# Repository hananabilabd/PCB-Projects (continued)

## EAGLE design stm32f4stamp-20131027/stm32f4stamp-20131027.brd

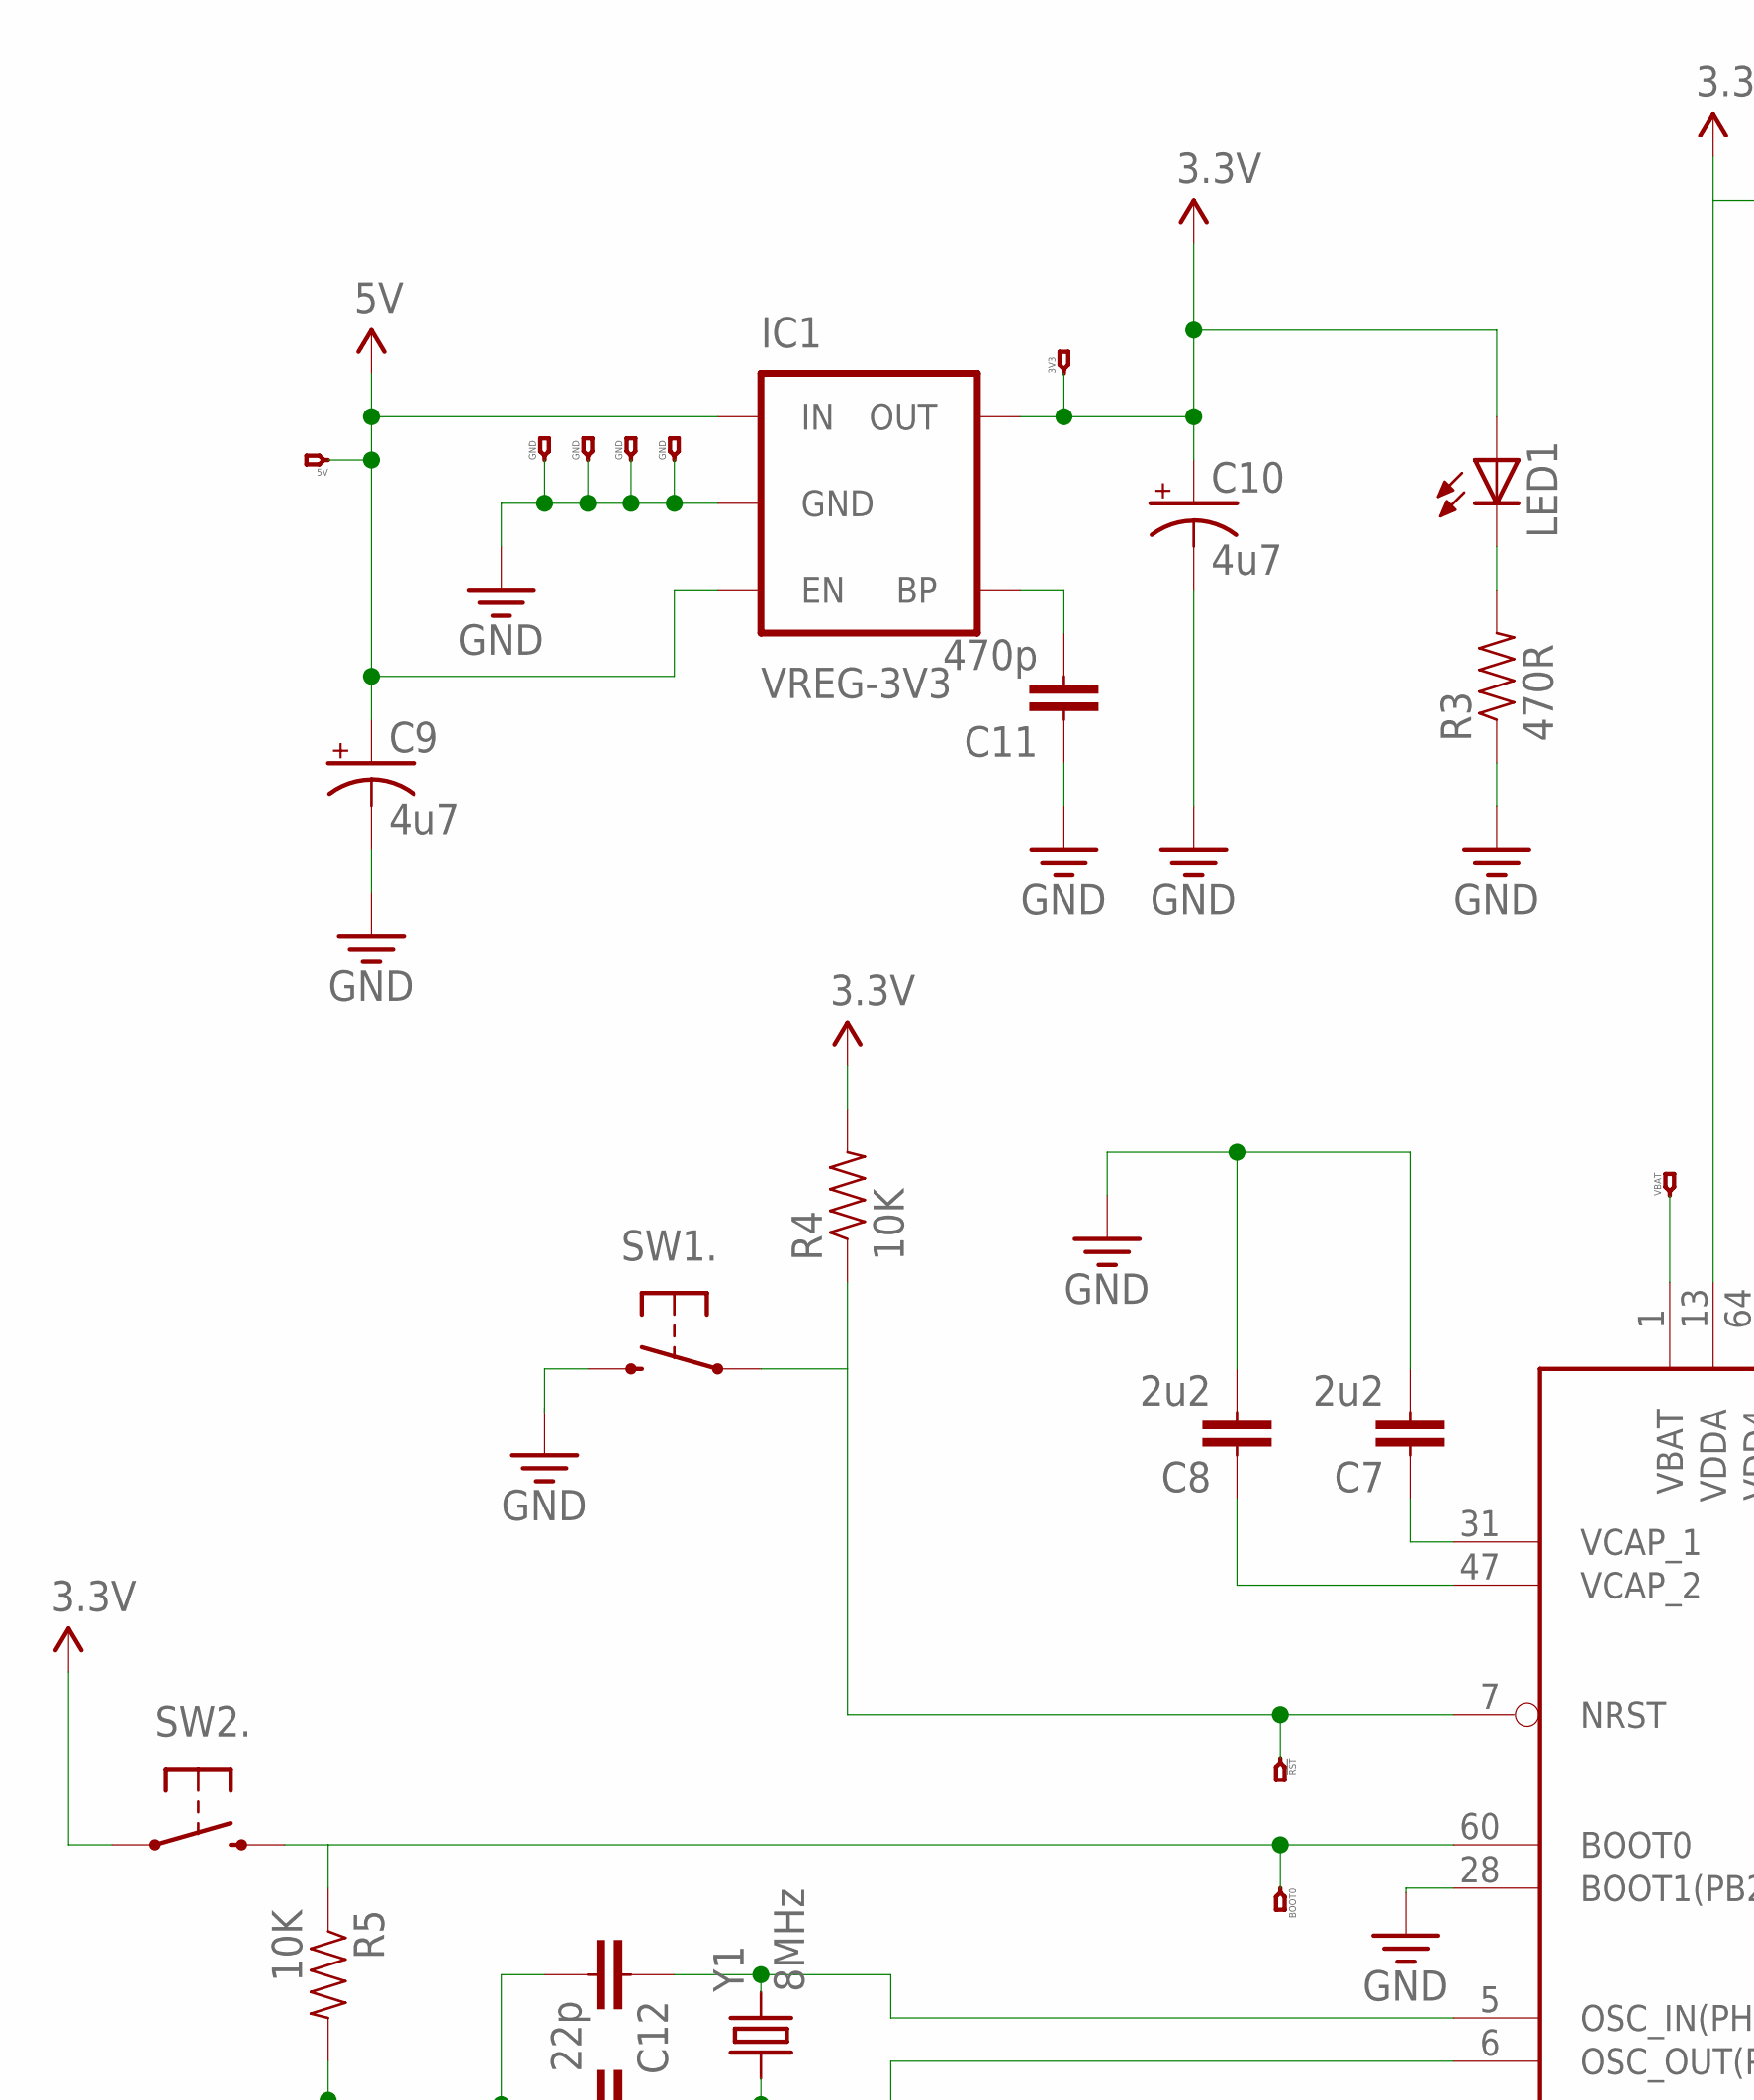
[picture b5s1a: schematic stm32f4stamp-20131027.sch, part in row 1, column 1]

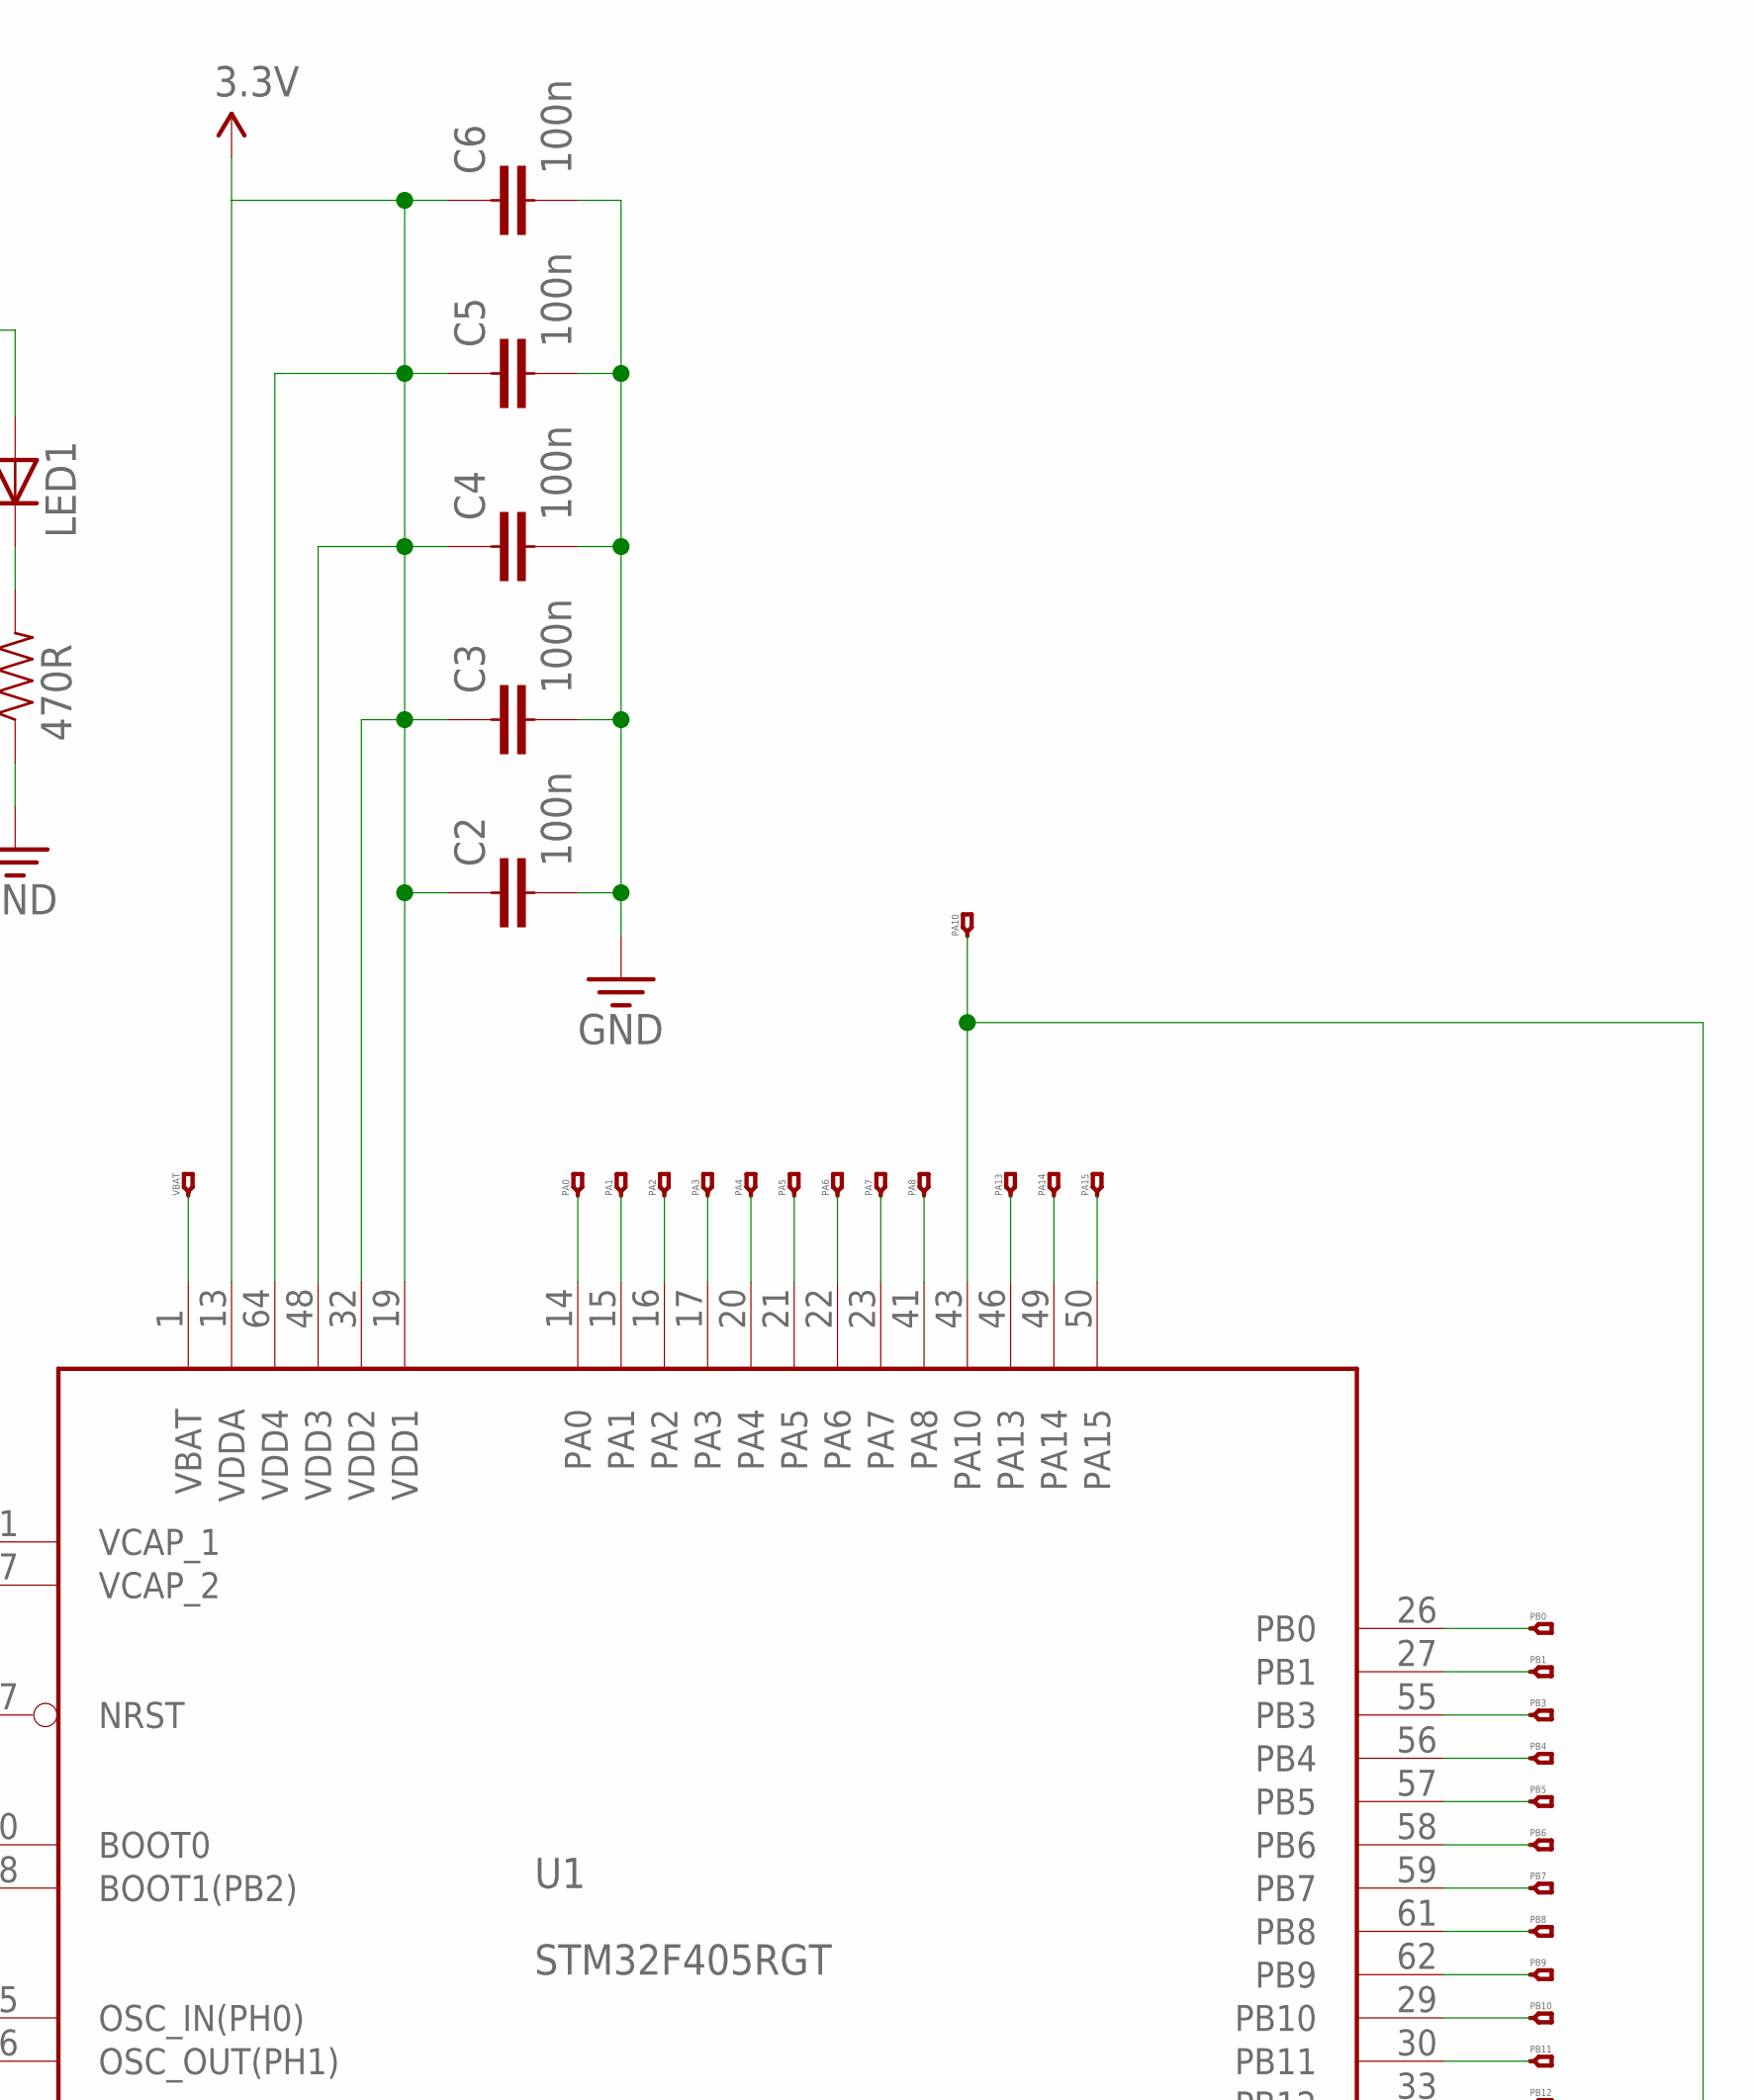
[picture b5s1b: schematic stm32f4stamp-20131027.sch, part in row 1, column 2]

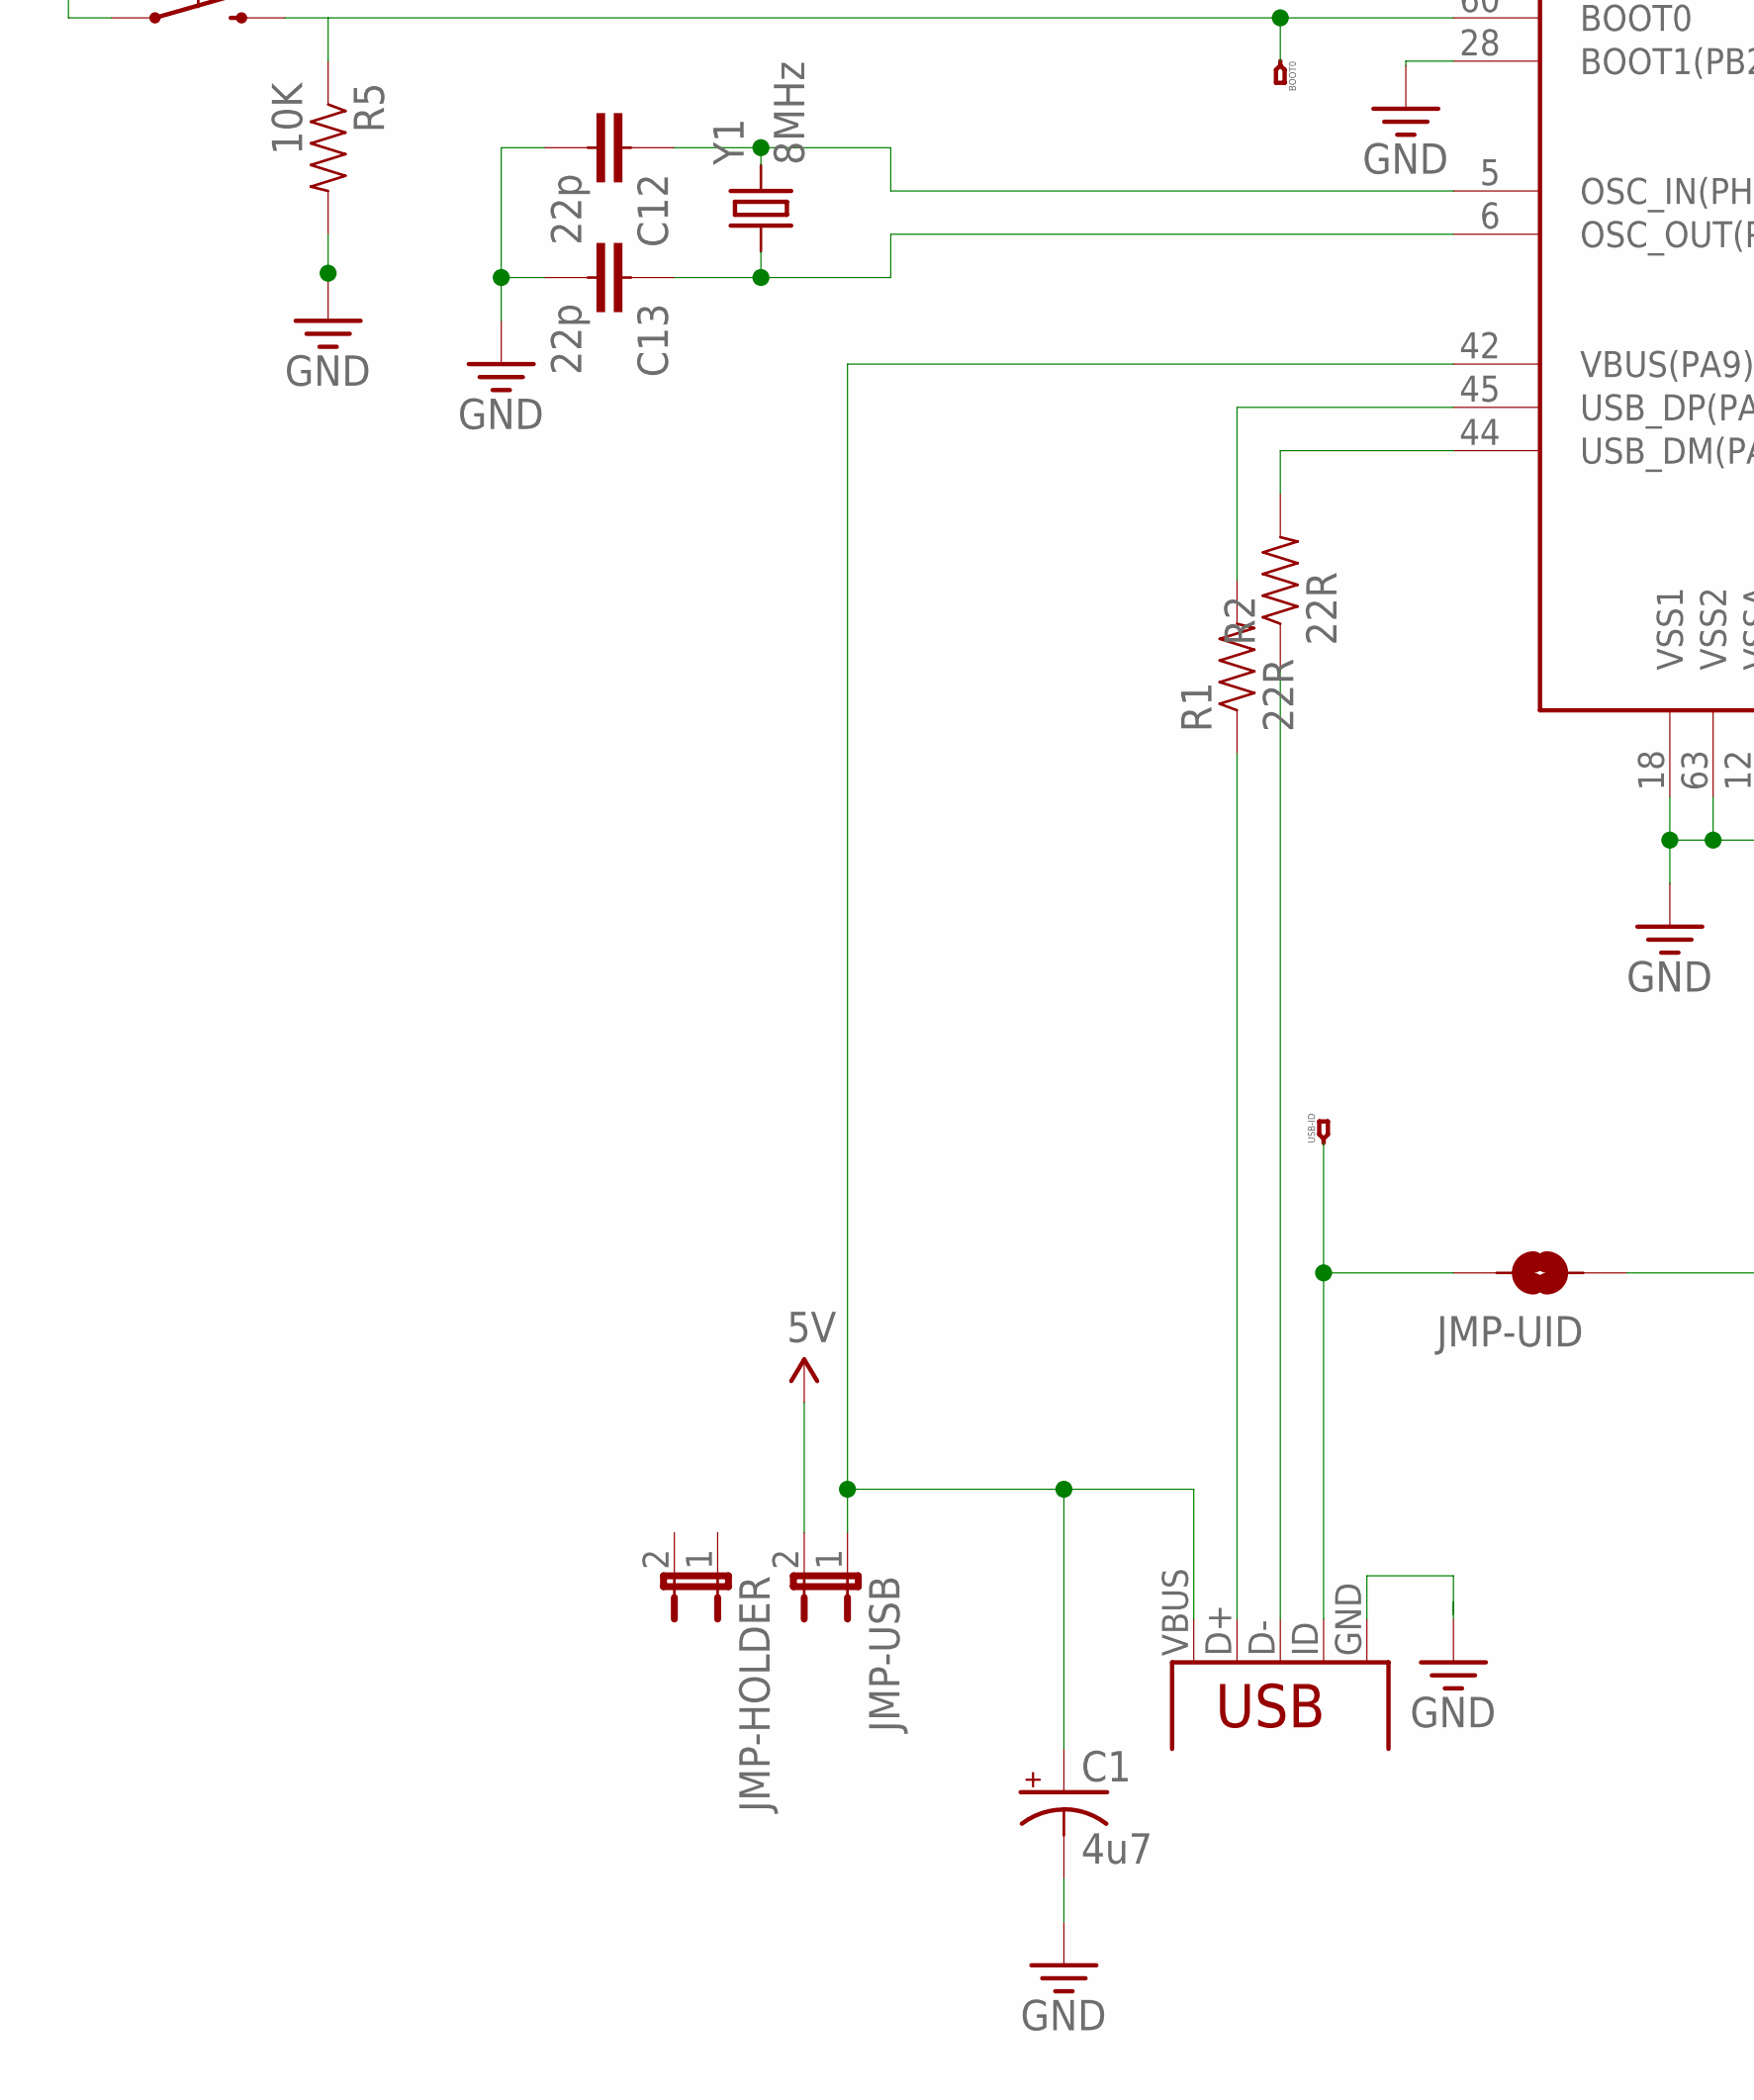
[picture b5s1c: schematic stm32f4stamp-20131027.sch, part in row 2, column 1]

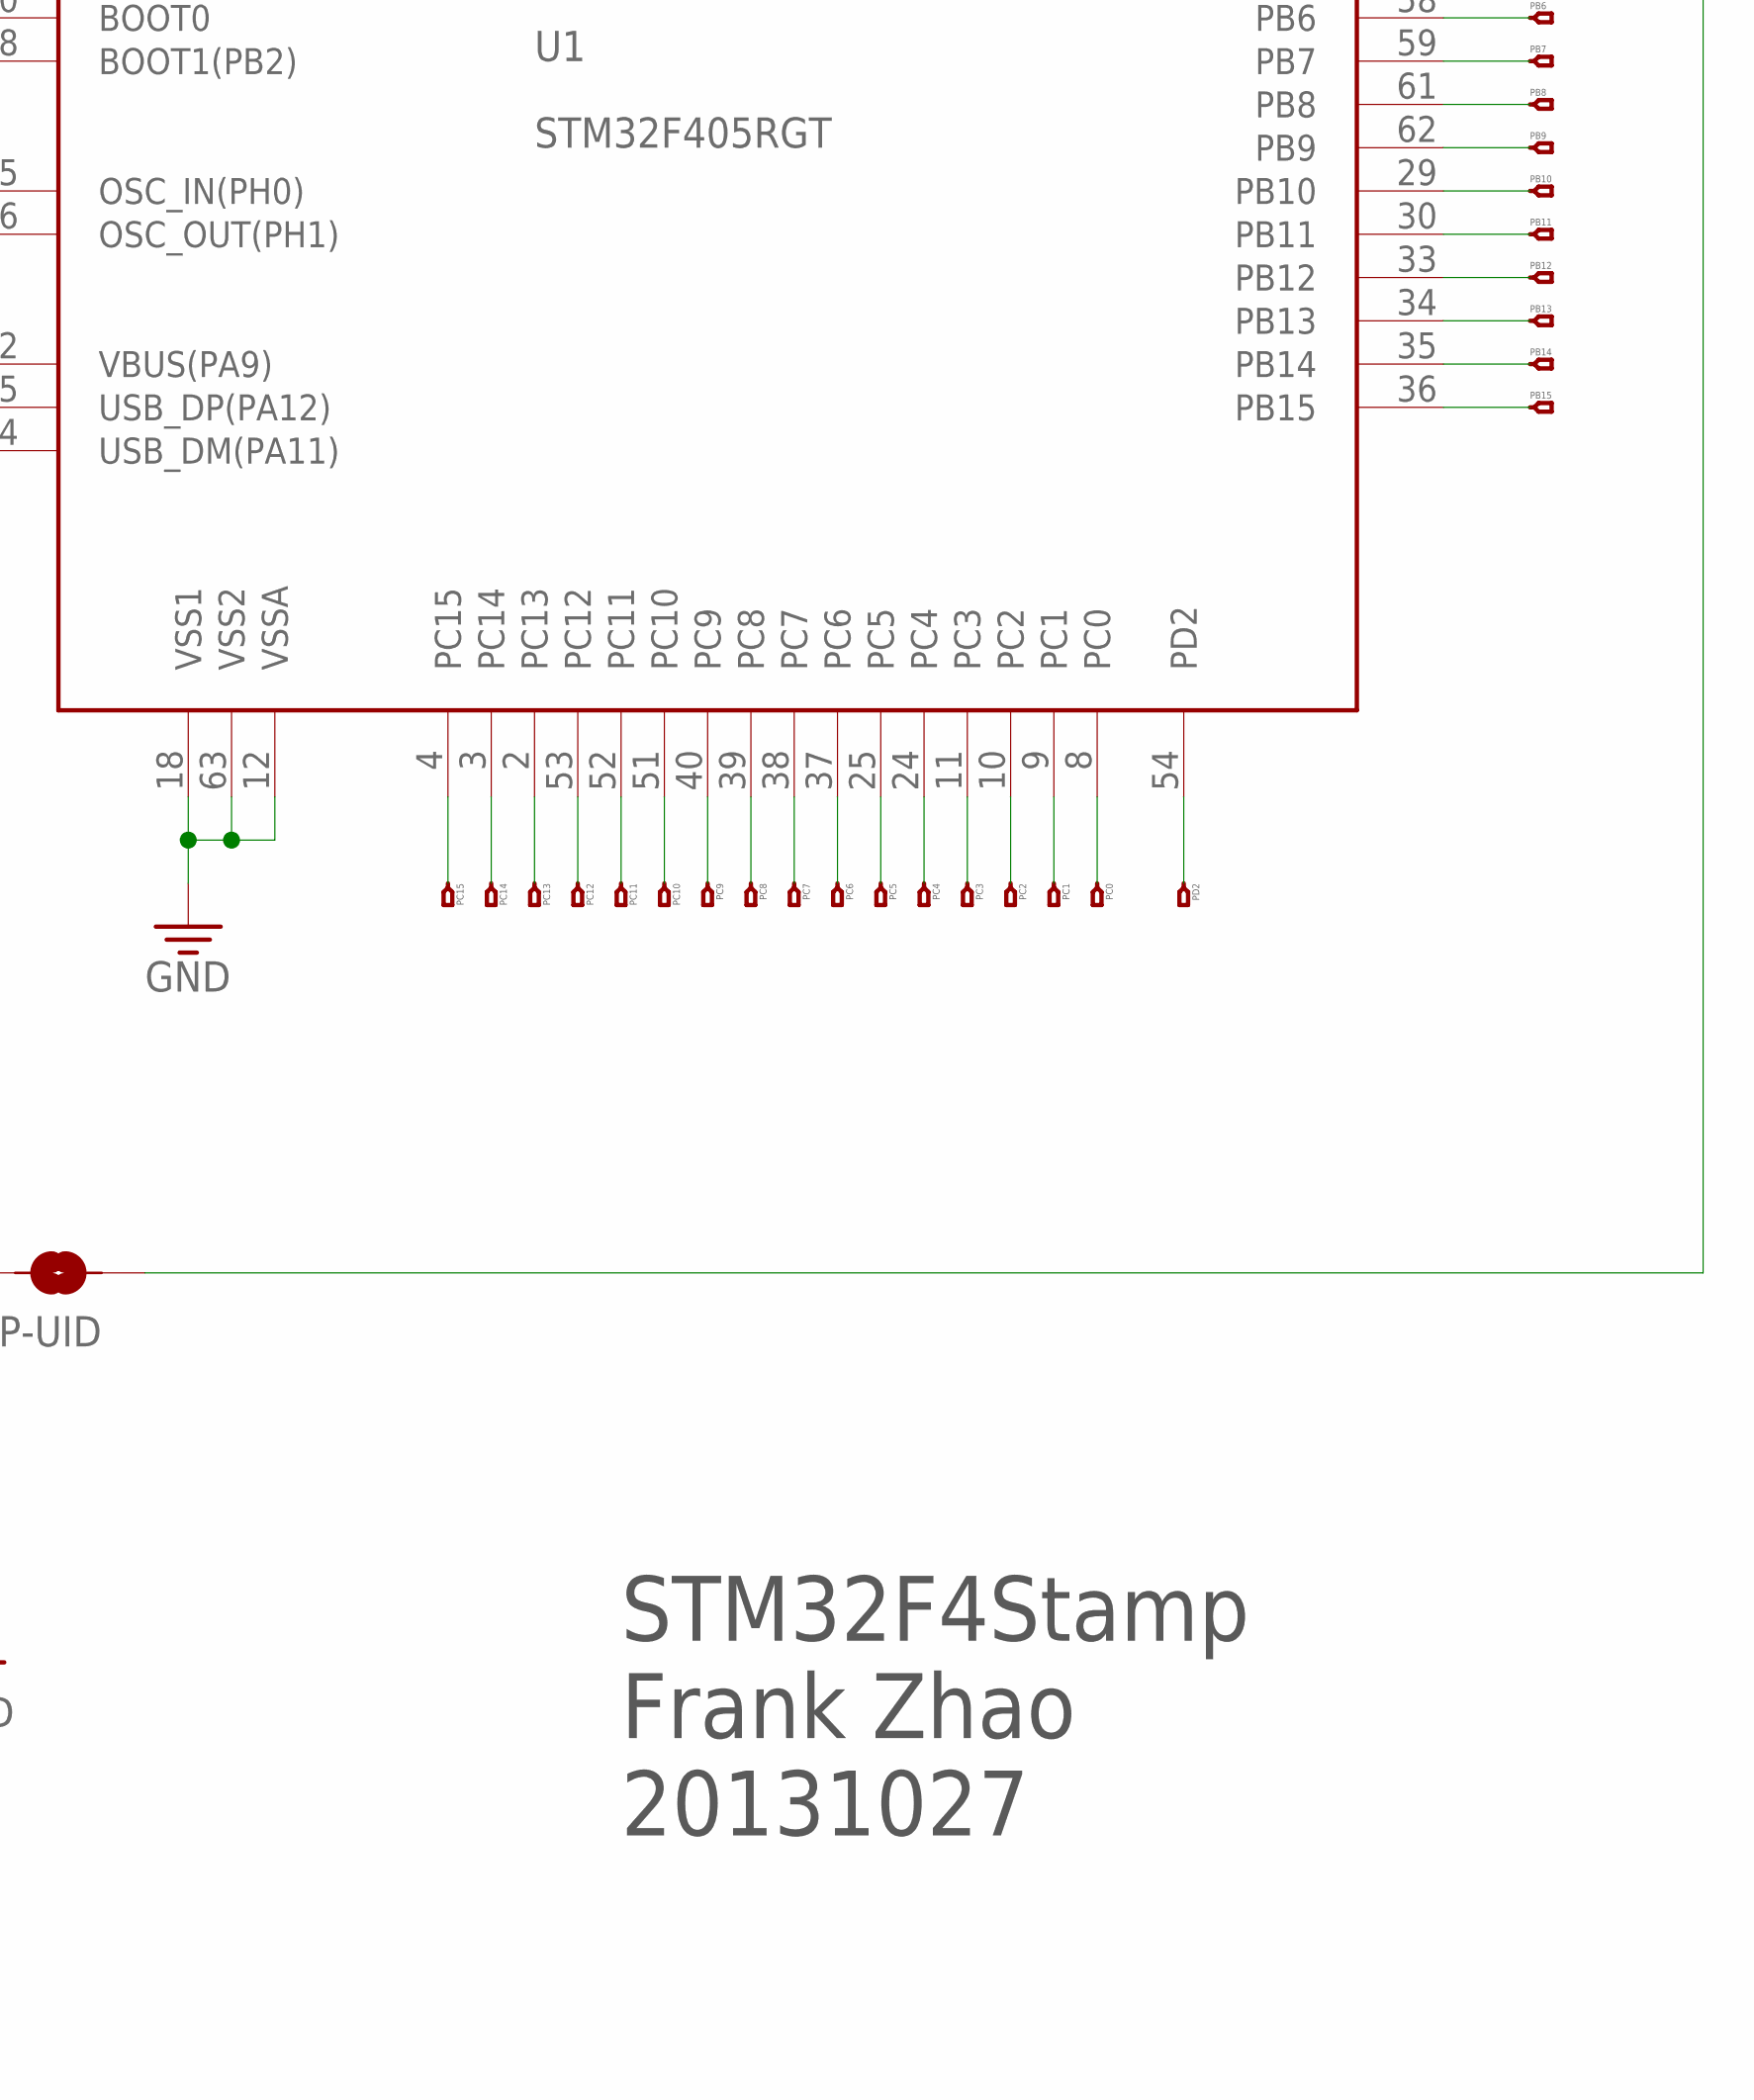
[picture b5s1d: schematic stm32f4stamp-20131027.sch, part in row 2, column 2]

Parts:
C1, C9, C10: 4u7; EIA3216-KIT
C2, C3, C4, C5, C6: 100n; 0603-CAP
C7, C8: 2u2; 0603-CAP
C11: 470p; 0603-CAP
C12, C13: 22p; 0603-CAP
IC1: VREG-3V3; SOT23-5
JMP-HOLDER: JUMPER-2-PTH-2MM; 1X02_2MM_TH
JMP-UID: SOLDERJUMPERNC; SJ_2S
JMP-USB: JUMPER-2-PTH-2MM; 1X02_2MM_TH
JP2: 5V; 1X1-HEADER-HOLE
JP3, JP5, JP6, JP7: GND; 1X1-HEADER-HOLE
JP4: 3V3; 1X1-HEADER-HOLE
JP8: PB8; 1X1-HEADER-HOLE
JP9: PA10; 1X1-HEADER-HOLE
JP10: PA8; 1X1-HEADER-HOLE
JP11: PA13; 1X1-HEADER-HOLE
JP12: PC9; 1X1-HEADER-HOLE
JP13: PC15; 1X1-HEADER-HOLE
JP14: PC14; 1X1-HEADER-HOLE
JP15: PC13; 1X1-HEADER-HOLE
JP16: PC12; 1X1-HEADER-HOLE
JP17: PC11; 1X1-HEADER-HOLE
JP18: PC10; 1X1-HEADER-HOLE
JP19: PC8; 1X1-HEADER-HOLE
JP20: PC7; 1X1-HEADER-HOLE
JP21: PC6; 1X1-HEADER-HOLE
JP22: PC5; 1X1-HEADER-HOLE
JP23: PC4; 1X1-HEADER-HOLE
JP24: PC3; 1X1-HEADER-HOLE
JP25: PC2; 1X1-HEADER-HOLE
JP26: PC1; 1X1-HEADER-HOLE
JP27: PC0; 1X1-HEADER-HOLE
JP28: PD2; 1X1-HEADER-HOLE
JP29: PA0; 1X1-HEADER-HOLE
JP30: PA1; 1X1-HEADER-HOLE
JP31: PA2; 1X1-HEADER-HOLE
JP32: PA3; 1X1-HEADER-HOLE
JP33: PA4; 1X1-HEADER-HOLE
JP34: PA5; 1X1-HEADER-HOLE
JP35: PA6; 1X1-HEADER-HOLE
JP36: PA7; 1X1-HEADER-HOLE
JP37: PA14; 1X1-HEADER-HOLE
JP38: PA15; 1X1-HEADER-HOLE
JP39: PB0; 1X1-HEADER-HOLE
JP40: PB1; 1X1-HEADER-HOLE
JP41: PB3; 1X1-HEADER-HOLE
JP42: PB4; 1X1-HEADER-HOLE
JP43: PB5; 1X1-HEADER-HOLE
JP44: PB6; 1X1-HEADER-HOLE
JP45: PB7; 1X1-HEADER-HOLE
JP46: PB9; 1X1-HEADER-HOLE
JP47: PB10; 1X1-HEADER-HOLE
JP48: PB11; 1X1-HEADER-HOLE
JP49: PB12; 1X1-HEADER-HOLE
JP50: PB13; 1X1-HEADER-HOLE
JP51: PB14; 1X1-HEADER-HOLE
JP52: PB15; 1X1-HEADER-HOLE
JP53: VBAT; 1X1-HEADER-HOLE
JP54: !RST; 1X1-HEADER-HOLE
JP55: BOOT0; 1X1-HEADER-HOLE
JP56: USB-ID; 1X1-HEADER-HOLE
LED1: LED0603; LED-0603
R1, R2: 22R; 0603-RES
R3: 470R; 0603-RES
R4, R5: 10K; 0603-RES
SW1: !RST; SWITCH-TACT-B3U-1100P-B
SW2: BOOT; SWITCH-TACT-B3U-1100P-B
U1: STM32F405RGT; LQFP64
USB: USB-MICROB-SMD
Y1: 8MHz; CRYSTAL-SMD-5X3

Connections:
3.3V: C2.1, C3.1, C4.1, C5.1, C6.1, C10.A (+), IC1.5 (OUT), JP4.1, LED1.A, R4.2, SW2.1, U1.13 (VDDA), U1.19 (VDD1), U1.32 (VDD2), U1.48 (VDD3), U1.64 (VDD4)
5V: C9.A (+), IC1.1 (IN), IC1.3 (EN), JMP-USB.2, JP2.1
GND: C1.C (-), C2.2, C3.2, C4.2, C5.2, C6.2, C7.2, C8.2, C9.C (-), C10.C (-), C11.1, C12.2, C13.2, IC1.2 (GND), JP3.1, JP5.1, JP6.1, JP7.1, R3.1, R5.2, SW1.2, SW1.BOSS, SW2.BOSS, U1.12 (VSSA), U1.18 (VSS1), U1.28 (BOOT1(PB2)), U1.63 (VSS2), USB.GND, USB.MT1, USB.MT2, USB.MT3, USB.MT4
unnamed: R1.2, U1.45 (USB_DP(PA12))
unnamed: R2.2, U1.44 (USB_DM(PA11))
unnamed: C1.A (+), JMP-USB.1, U1.42 (VBUS(PA9)), USB.VBUS
unnamed: JP12.1, U1.40 (PC9)
unnamed: R1.1, USB.D+
unnamed: R2.1, USB.D-
unnamed: JP8.1, U1.61 (PB8)
unnamed: C11.2, IC1.4 (BP)
unnamed: JP10.1, U1.41 (PA8)
unnamed: JP11.1, U1.46 (PA13)
unnamed: C13.1, U1.6 (OSC_OUT(PH1)), Y1.1
unnamed: C7.1, U1.31 (VCAP_1)
unnamed: C8.1, U1.47 (VCAP_2)
unnamed: C12.1, U1.5 (OSC_IN(PH0)), Y1.3 (2)
unnamed: JP55.1, R5.1, SW2.2, U1.60 (BOOT0)
unnamed: JP54.1, R4.1, SW1.1, U1.7 (NRST)
unnamed: LED1.C, R3.2
unnamed: JMP-UID.2, JP56.1, USB.ID
unnamed: JMP-UID.1, JP9.1, U1.43 (PA10)
unnamed: JP13.1, U1.4 (PC15)
unnamed: JP14.1, U1.3 (PC14)
unnamed: JP15.1, U1.2 (PC13)
unnamed: JP16.1, U1.53 (PC12)
unnamed: JP17.1, U1.52 (PC11)
unnamed: JP18.1, U1.51 (PC10)
unnamed: JP19.1, U1.39 (PC8)
unnamed: JP20.1, U1.38 (PC7)
unnamed: JP21.1, U1.37 (PC6)
unnamed: JP22.1, U1.25 (PC5)
unnamed: JP23.1, U1.24 (PC4)
unnamed: JP24.1, U1.11 (PC3)
unnamed: JP25.1, U1.10 (PC2)
unnamed: JP26.1, U1.9 (PC1)
unnamed: JP27.1, U1.8 (PC0)
unnamed: JP28.1, U1.54 (PD2)
unnamed: JP29.1, U1.14 (PA0)
unnamed: JP30.1, U1.15 (PA1)
unnamed: JP31.1, U1.16 (PA2)
unnamed: JP32.1, U1.17 (PA3)
unnamed: JP33.1, U1.20 (PA4)
unnamed: JP34.1, U1.21 (PA5)
unnamed: JP35.1, U1.22 (PA6)
unnamed: JP36.1, U1.23 (PA7)
unnamed: JP37.1, U1.49 (PA14)
unnamed: JP38.1, U1.50 (PA15)
unnamed: JP39.1, U1.26 (PB0)
unnamed: JP40.1, U1.27 (PB1)
unnamed: JP41.1, U1.55 (PB3)
unnamed: JP42.1, U1.56 (PB4)
unnamed: JP43.1, U1.57 (PB5)
unnamed: JP44.1, U1.58 (PB6)
unnamed: JP45.1, U1.59 (PB7)
unnamed: JP46.1, U1.62 (PB9)
unnamed: JP47.1, U1.29 (PB10)
unnamed: JP48.1, U1.30 (PB11)
unnamed: JP49.1, U1.33 (PB12)
unnamed: JP50.1, U1.34 (PB13)
unnamed: JP51.1, U1.35 (PB14)
unnamed: JP52.1, U1.36 (PB15)
unnamed: JP53.1, U1.1 (VBAT)

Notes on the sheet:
STM32F4Stamp Frank Zhao 20131027

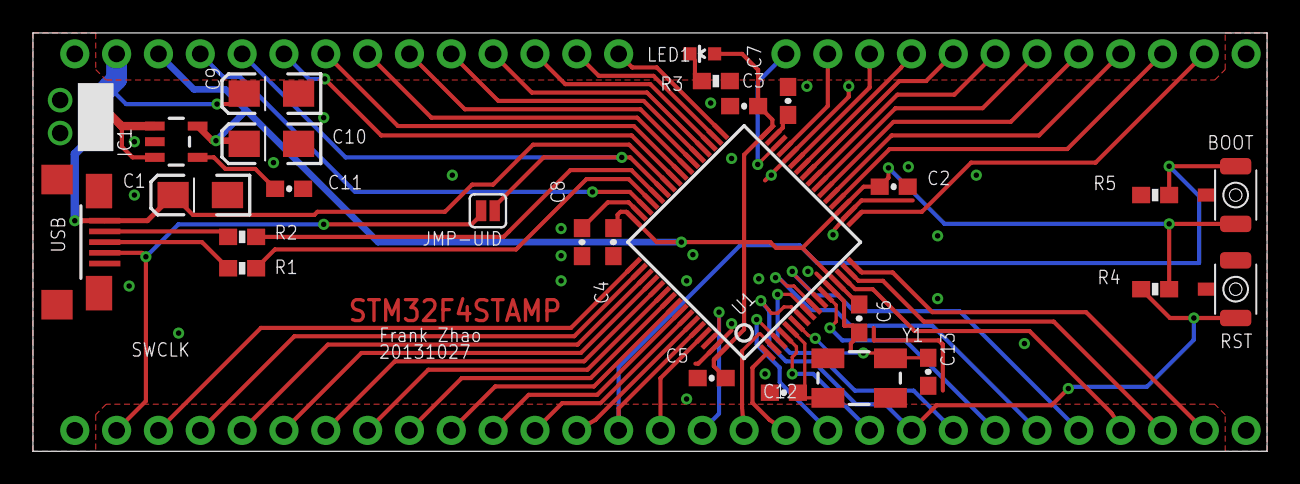
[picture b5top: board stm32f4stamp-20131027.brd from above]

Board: 2 copper layers, 74.9 x 25.4 mm, 83 parts (0 on the bottom side), 63 nets.
